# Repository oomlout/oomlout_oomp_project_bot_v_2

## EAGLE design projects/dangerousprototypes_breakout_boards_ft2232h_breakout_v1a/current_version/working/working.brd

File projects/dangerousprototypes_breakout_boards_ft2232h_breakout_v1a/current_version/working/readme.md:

# breakout_boards
 
## summary 
* id: dangerousprototypes_breakout_boards_ft2232h_breakout_v1a
* user: dangerousprototypes
* name: breakout_boards
* board: ft2232h_breakout_v1a
* repo: https://github.com/DangerousPrototypes/Breakout_Boards

* src_file_repo_sch: 
* src_file_repo_sch_link: https://github.com/DangerousPrototypes/Breakout_Boards/tree/master/
* full details link: https://github.com/oomlout/oomlout_oomp_project_bot_v_2/tree/main/projects/dangerousprototypes_breakout_boards_ft2232h_breakout_v1a/current_version/working

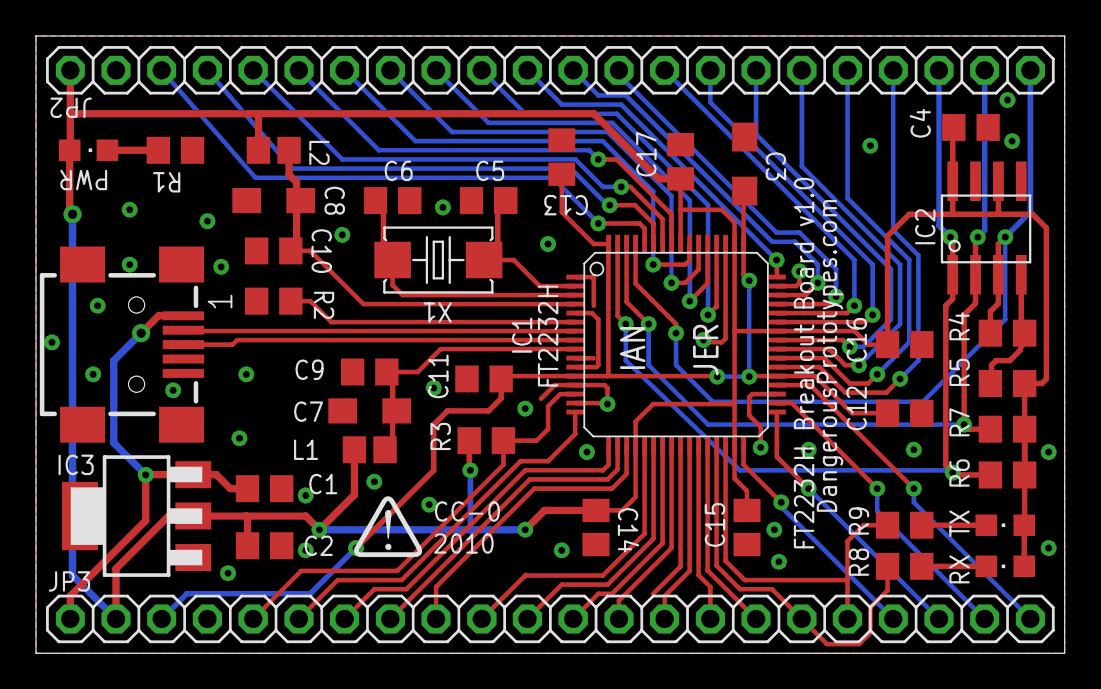
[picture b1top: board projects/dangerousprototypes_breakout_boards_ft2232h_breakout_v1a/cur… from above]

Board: 2 copper layers, 57.1 x 34.3 mm, 40 parts (1 on the bottom side), 53 nets.

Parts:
C1, C2, C4, C9, C10, C11, C12, C13, C14, C15, C16, C17: 0.1uF; C805
C3: 3.3uF; SMC_A
C5, C6: 27pF; C805
C7, C8: 4.7uF; SMC_A
CONN1: CONN_USB; CONN_USB_MINI-B
IC1: FT2232H; LQFP64
IC2: 93C46; SOIC8
IC3: SOT223
JP2, JP3: 1X22
L1, L2: FB805
PWR: LED-805
R1, R8, R9: 470; R805
R2: 12k 1%; R805
R3, R5, R6, R7: 10k; R805
R4: 2.2k; R805
RX: LED-805
TX: LED-805
U$7, U$8: DP_LOGO
X1: 12MHz; 4X6

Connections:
1.8V: C3.+, C11.1, C12.1, C13.1, IC1.12, IC1.37, IC1.49, IC1.64, JP3.3
3.3V: C2.1, C4.1, C14.1, C15.1, C16.1, C17.1, IC1.20, IC1.31, IC1.42, IC1.50, IC1.56, IC2.6, IC2.8, IC3.2, JP2.1, JP3.2, L1.2, L2.2, PWR.A, R3.1, R5.2, R6.2, R7.2, RX.A, TX.A
5V: C1.1, CONN1.VUSB, IC3.3, JP3.1
!PWEREN: IC1.60, JP2.3
!RESET: IC1.14, JP3.5, R3.2
!SUSPEND: IC1.36, JP3.22
AC0: IC1.26, JP3.14
AC1: IC1.27, JP3.15
AC2: IC1.28, JP3.16
AC3: IC1.29, JP3.17, R8.1
AC4: IC1.30, JP3.18, R9.1
AC5: IC1.32, JP3.19
AC6: IC1.33, JP3.20
AC7: IC1.34, JP3.21
AD0: IC1.16, JP3.6
AD1: IC1.17, JP3.7
AD2: IC1.18, JP3.8
AD3: IC1.19, JP3.9
AD4: IC1.21, JP3.10
AD5: IC1.22, JP3.11
AD6: IC1.23, JP3.12
AD7: IC1.24, JP3.13
BC0: IC1.48, JP2.11
BC1: IC1.52, JP2.10
BC2: IC1.53, JP2.9
BC3: IC1.54, JP2.8
BC4: IC1.55, JP2.7
BC5: IC1.57, JP2.6
BC6: IC1.58, JP2.5
BC7: IC1.59, JP2.4
BD0: IC1.38, JP2.19
BD1: IC1.39, JP2.18
BD2: IC1.40, JP2.17
BD3: IC1.41, JP2.16
BD4: IC1.43, JP2.15
BD5: IC1.44, JP2.14
BD6: IC1.45, JP2.13
BD7: IC1.46, JP2.12
DM: CONN1.D-, IC1.7
DP: CONN1.D+, IC1.8
EECLK: IC1.62, IC2.2, JP2.21, R7.1
EECS: IC1.63, IC2.1, JP2.20, R6.1
EEDATA: IC1.61, IC2.3, JP2.22, R4.2
GND: C1.2, C2.2, C3.-, C4.2, C5.2, C6.2, C7.-, C8.-, C9.2, C10.2, C11.2, C12.2, C13.2, C14.2, C15.2, C16.2, C17.2, CONN1.GND, IC1.1, IC1.5, IC1.10, IC1.11, IC1.13, IC1.15, IC1.25, IC1.35, IC1.47, IC1.51, IC2.5, IC3.1, JP2.2, JP3.4, R1.1, R2.1
unnamed: PWR.C, R1.2
unnamed: R8.2, RX.C
unnamed: R9.2, TX.C
unnamed: IC1.6, R2.2
unnamed: C5.1, IC1.2, X1.1
unnamed: C6.1, IC1.3, X1.2
unnamed: IC2.4, R4.1, R5.1
unnamed: C8.+, C10.1, IC1.4, L2.1
unnamed: C7.+, C9.1, IC1.9, L1.1

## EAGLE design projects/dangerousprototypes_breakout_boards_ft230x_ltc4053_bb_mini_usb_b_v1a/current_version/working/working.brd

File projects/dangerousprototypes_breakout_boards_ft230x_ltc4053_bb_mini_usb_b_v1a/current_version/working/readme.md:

# breakout_boards
 
## summary 
* id: dangerousprototypes_breakout_boards_ft230x_ltc4053_bb_mini_usb_b_v1a
* user: dangerousprototypes
* name: breakout_boards
* board: ft230x_ltc4053_bb_mini_usb_b_v1a
* repo: https://github.com/DangerousPrototypes/Breakout_Boards

* src_file_repo_sch: 
* src_file_repo_sch_link: https://github.com/DangerousPrototypes/Breakout_Boards/tree/master/
* full details link: https://github.com/oomlout/oomlout_oomp_project_bot_v_2/tree/main/projects/dangerousprototypes_breakout_boards_ft230x_ltc4053_bb_mini_usb_b_v1a/current_version/working

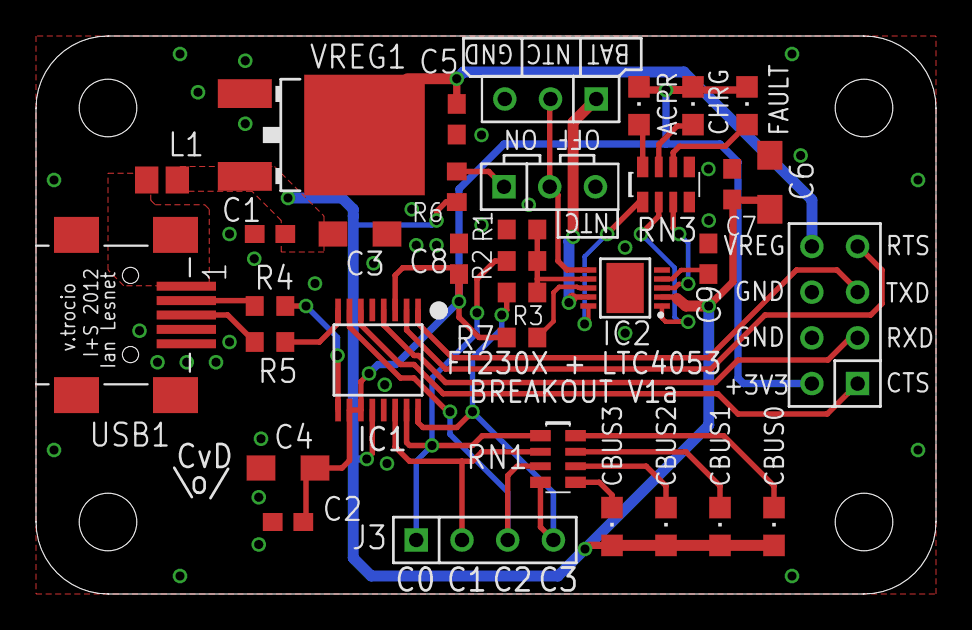
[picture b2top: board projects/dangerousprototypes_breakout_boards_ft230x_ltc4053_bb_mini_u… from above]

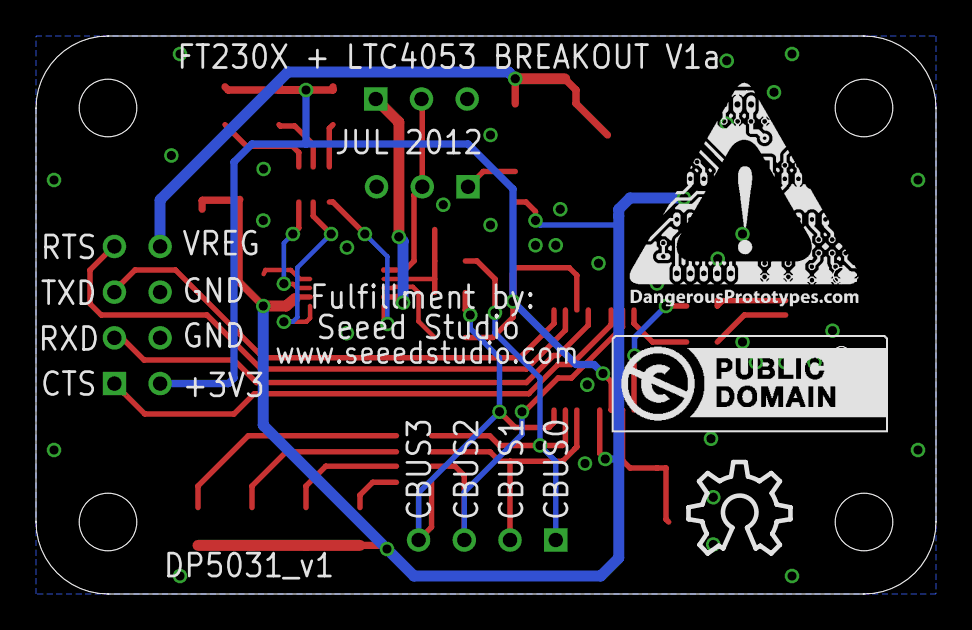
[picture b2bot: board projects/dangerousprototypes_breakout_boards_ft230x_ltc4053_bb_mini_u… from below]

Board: 2 copper layers, 50.0 x 31.0 mm, 39 parts (3 on the bottom side), 33 nets.

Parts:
ACPR: LED-805
C1, C2: C603
C3, C4: SMC_A
C5, C7, C8, C9: 0.1uF; C603
C6: 4.7uF 10V; SMC_A
CHRG: LED-805
D1, D2, D3, D4: LED-805
FAULT: LED-805
IC1: IC_FT230X-SSOP-16; SSOP-16-FTDI
IC2: IC_LTC4053-MSOP-10; MSOP-10
J1, J4: CON_HEADER_1X03-PTH; M1X3
J3: CON_HEADER_1X04; M1X4
J5: CON_HEADER_2X04-PTH; M2X4
L1: 600R 2A; FB603
PCB1: PCB_DP_RECTANGLE-31X50; DP5031_V1
R1: 16.5K 1%; R603
R2: 1.5K 1%; R603
R3, R6: 4.32K 1%; R603
R4, R5: 27R; R603
R7: 10K; R603
RN1: RN8P-4R-CRA06S
RN3: 470R; RN8P-4R-CRA06S
U$1: FRAME_DINA4_L; DP_LOGO
U$3: DP_LOGO_ART_0.5X0.5
U$4: LOGO_CC-0
U$5: OSHW_10X200_NOTEXT
USB1: CON-USB-F-MINI-B; CONN_USB_MINI-B
VREG1: DPAK

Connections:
+3V3: ACPR.C, C2.1, C4.+, C8.1, CHRG.C, FAULT.C, IC1.3, IC1.10, IC1.11, J5.2, R7.2
BAT: IC2.P9, J1.1
CBUS0: IC1.15, J3.1, R2.2, RN1.1
CBUS1: IC1.14, J3.2, RN1.2
CBUS2: IC1.7, J3.3, RN1.3
CBUS3: IC1.16, J3.4, R3.2, RN1.4
CTS: IC1.6, J5.1
GND: C1.2, C2.2, C3.-, C4.-, C5.2, C6.-, C7.2, C8.2, C9.2, IC1.5, IC1.13, IC2.P5, IC2.P11, J1.3, J4.3, J5.4, J5.6, R1.1, USB1.GND, VREG1.1
unnamed: IC2.P10, RN3.1
unnamed: IC2.P7, R1.2, R2.1, R3.1
unnamed: IC2.P1, RN3.2
unnamed: IC2.P3, RN3.3
unnamed: D1.C, RN1.8
unnamed: D2.C, RN1.7
unnamed: D3.C, RN1.6
unnamed: D4.C, RN1.5
unnamed: IC2.P8, R7.1
unnamed: J4.1, R6.1
unnamed: IC1.9, R4.2
unnamed: IC1.8, R5.2
unnamed: C9.1, IC2.P4
unnamed: FAULT.A, RN3.6
unnamed: CHRG.A, RN3.7
unnamed: ACPR.A, RN3.8
NTC: IC2.P6, J1.2, J4.2
RTS: IC1.2, J5.7
RXD: IC1.4, J5.3
TXD: IC1.1, J5.5
USBD+: R5.1, USB1.D+
USBD-: R4.1, USB1.D-
V+: C1.1, C3.+, C6.+, C7.1, D1.A, D2.A, D3.A, D4.A, IC1.12, IC2.P2, L1.1, R6.2, VREG1.3
VREG: C5.1, J5.8, VREG1.2
VUSBE: L1.2, USB1.VUSB

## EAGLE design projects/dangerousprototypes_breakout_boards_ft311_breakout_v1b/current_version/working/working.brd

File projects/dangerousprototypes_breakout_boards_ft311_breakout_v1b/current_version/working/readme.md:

# breakout_boards
 
## summary 
* id: dangerousprototypes_breakout_boards_ft311_breakout_v1b
* user: dangerousprototypes
* name: breakout_boards
* board: ft311_breakout_v1b
* repo: https://github.com/DangerousPrototypes/Breakout_Boards

* src_file_repo_sch: 
* src_file_repo_sch_link: https://github.com/DangerousPrototypes/Breakout_Boards/tree/master/
* full details link: https://github.com/oomlout/oomlout_oomp_project_bot_v_2/tree/main/projects/dangerousprototypes_breakout_boards_ft311_breakout_v1b/current_version/working

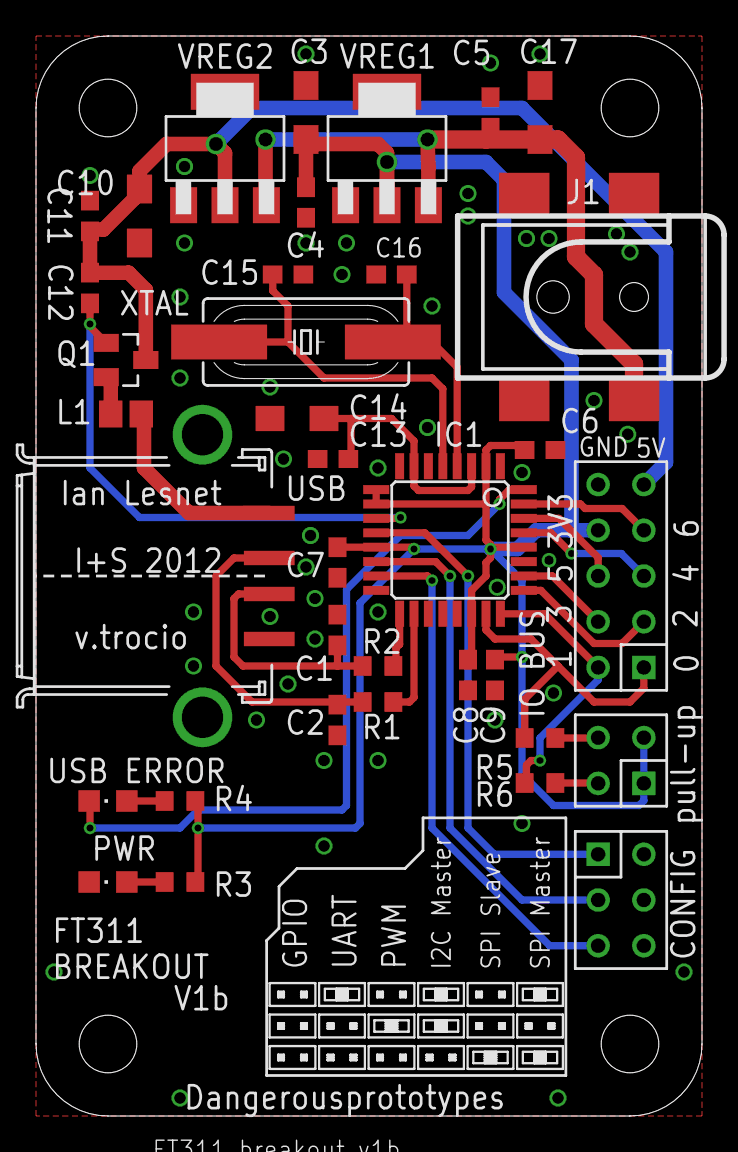
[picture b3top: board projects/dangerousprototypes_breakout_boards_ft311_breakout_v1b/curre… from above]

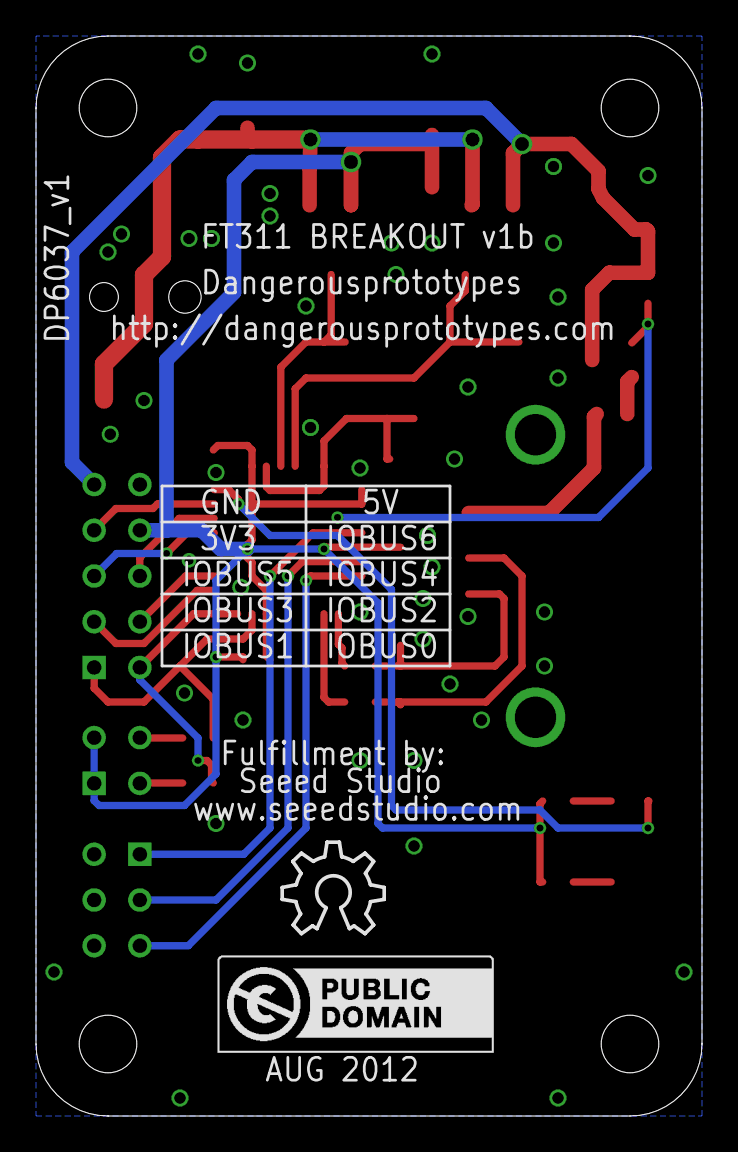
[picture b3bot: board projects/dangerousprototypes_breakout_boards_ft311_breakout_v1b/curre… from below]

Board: 2 copper layers, 37.0 x 60.0 mm, 62 parts (2 on the bottom side), 29 nets.

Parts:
C1, C2: 47pF; C603
C3, C10, C14, C17: 10uF; SMC_A
C4, C5, C6, C7, C8, C9, C11, C12, C13: 0.1uF; C603
C15, C16: 18pF; C603
IC1: IC_FT311D-LQFP-32; LQFP-32
J1: DC_BARREL_JACK_SMD_2MM
J2: CON_HEADER_2X03-PTH; M2X3
J3: CON_HEADER_2X02-PTH; M2X2
J4: CON_HEADER_2X05-PTH; M2X5
L1: 1.7A; FB603
LED1: YELLOW; LED-805
LED2: RED; LED-805
PCB1: PCB_DP_RECTANGLE-37X60; DP6037_V1
Q1: SOT-23
R1, R2: 27R; R603
R3: 3.3K; R603
R4: 1.2K; R603
R5, R6: 10K; R603
U$1: FRAME_DINA4_L; DP_LOGO
U$2, U$4, U$10, U$11, U$12, U$13, U$14, U$15, U$16, U$17, U$19, U$23, U$25: JUMP2_DESC_OFF
U$3, U$5, U$6, U$7, U$8, U$9, U$18, U$22, U$24: JUMP2_DESC_ON
U$20: LOGO_CC-0
U$21: OSHW_8X200_NOTEXT
USB: CON-USB-F-2PB; CONN_USB_A_F
VREG1: LD1117S33; SOT-223
VREG2: LD1117S50; SOT-223
XTAL: 12Mhz; HC-49U

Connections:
!USB_ERR: IC1.32, LED2.C
!VBUSCTRL: C12.2, IC1.11, Q1.1
+1V8: C13.1, C14.+, IC1.3, IC1.7
+3V3: C3.+, C4.1, C6.1, C7.1, C8.1, C9.1, IC1.2, IC1.9, IC1.10, IC1.13, IC1.22, IC1.28, J3.1, J3.3, J4.8, R3.2, R4.2, VREG1.2
+5V: C10.+, C11.1, C12.1, J4.9, Q1.3, VREG2.2
CNFG0: IC1.12, J2.1
CNFG1: IC1.14, J2.3
CNFG2: IC1.15, J2.5
GND: C1.2, C2.2, C3.-, C4.2, C5.2, C6.2, C7.2, C8.2, C9.2, C10.-, C11.2, C13.2, C14.-, C15.2, C16.2, C17.-, IC1.1, IC1.6, IC1.8, IC1.16, IC1.19, IC1.27, J1.P2, J1.P3, J2.2, J2.4, J2.6, J4.10, LED1.C, USB.4, VREG1.1, VREG2.1
IOBUS0: IC1.23, J4.1, R5.1
IOBUS1: IC1.24, J4.2, R6.1
IOBUS2: IC1.25, J4.3
IOBUS3: IC1.26, J4.4
IOBUS4: IC1.29, J4.5
IOBUS5: IC1.30, J4.6
IOBUS6: IC1.31, J4.7
unnamed: IC1.18, R1.1
unnamed: IC1.17, R2.1
unnamed: C1.1, R2.2, USB.3
unnamed: C2.1, R1.2, USB.2
unnamed: L1.2, USB.1
unnamed: L1.1, Q1.2
unnamed: C16.1, IC1.4, XTAL.2
unnamed: C5.1, C17.+, J1.P1@2, VREG1.3, VREG2.3
unnamed: C15.1, IC1.5, XTAL.1
unnamed: LED1.A, R3.1
unnamed: LED2.A, R4.1
unnamed: J3.4, R5.2
unnamed: J3.2, R6.2

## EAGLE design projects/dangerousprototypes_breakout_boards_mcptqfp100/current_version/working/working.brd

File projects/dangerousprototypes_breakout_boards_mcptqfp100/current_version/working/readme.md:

# breakout_boards
 
## summary 
* id: dangerousprototypes_breakout_boards_mcptqfp100
* user: dangerousprototypes
* name: breakout_boards
* board: mcptqfp100
* repo: https://github.com/DangerousPrototypes/Breakout_Boards

* src_file_repo_sch: 
* src_file_repo_sch_link: https://github.com/DangerousPrototypes/Breakout_Boards/tree/master/
* full details link: https://github.com/oomlout/oomlout_oomp_project_bot_v_2/tree/main/projects/dangerousprototypes_breakout_boards_mcptqfp100/current_version/working

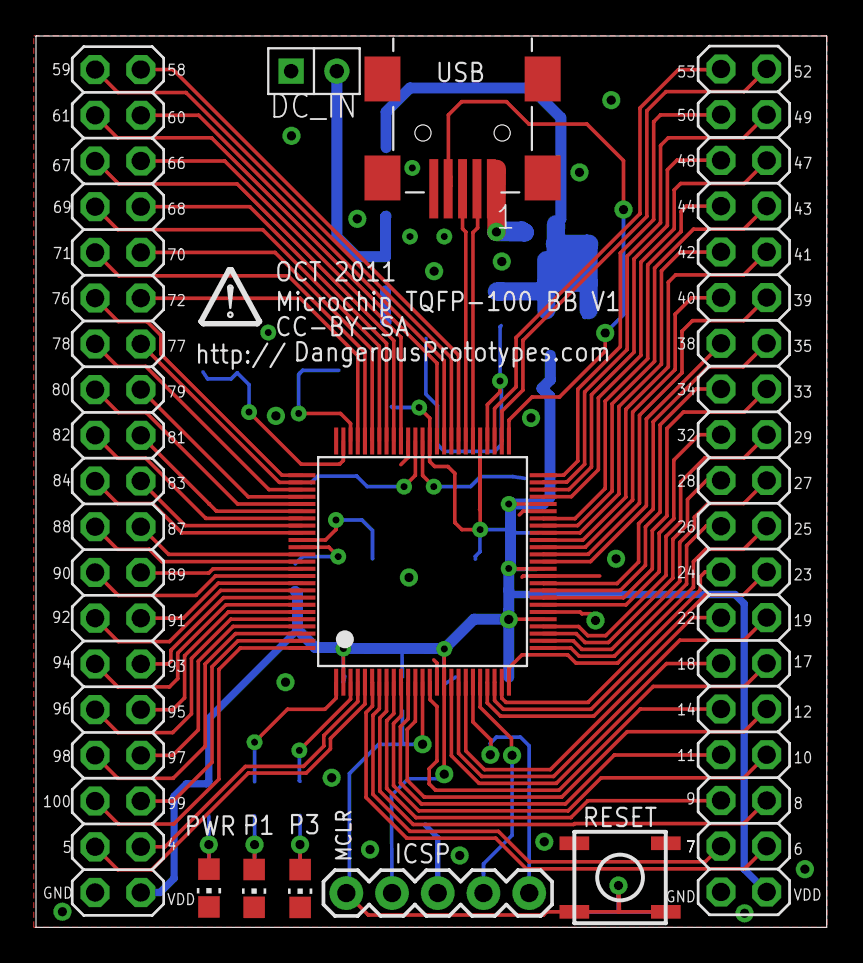
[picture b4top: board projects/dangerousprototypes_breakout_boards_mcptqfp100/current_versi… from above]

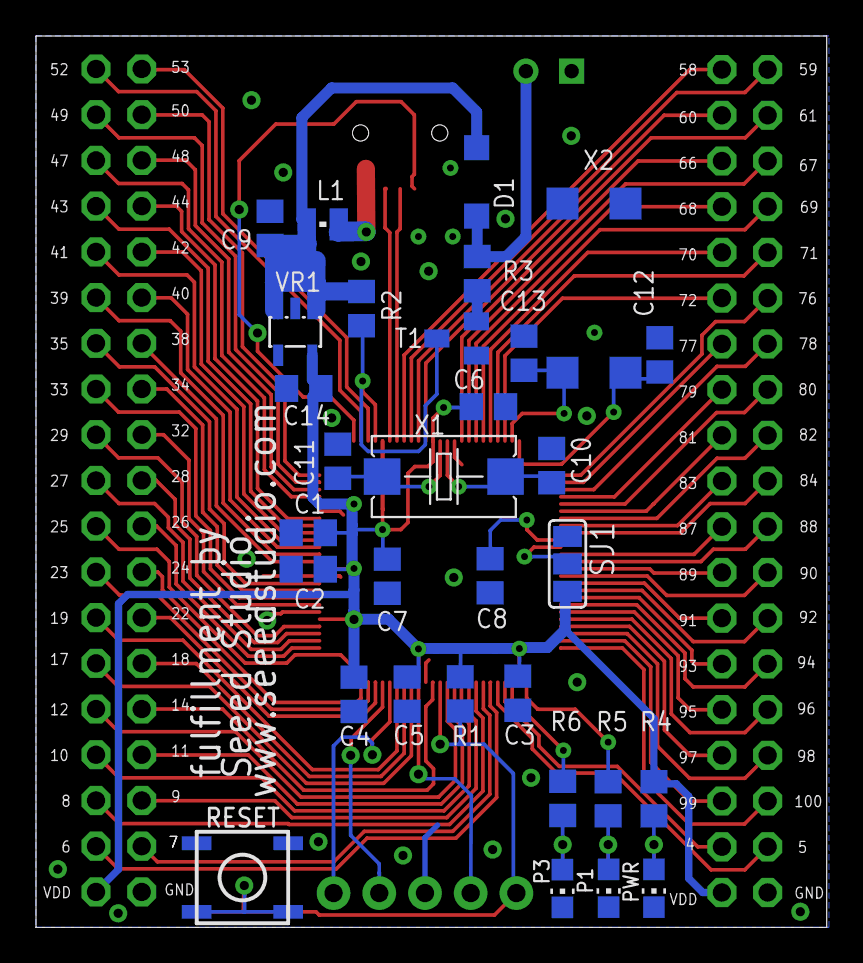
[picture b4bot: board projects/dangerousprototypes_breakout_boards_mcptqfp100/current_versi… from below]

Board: 2 copper layers, 43.9 x 49.5 mm, 42 parts (31 on the bottom side), 96 nets.

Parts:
C1, C2, C3, C4, C5, C6, C7: 0.1uF; C805
C8, C9, C10, C11, C12, C13: 10uF; C805
C14: 1uF; C805
D1: SOD123
DC_IN: HEADER1X2PTH; M1X2
IC1: PIC24FJ256GB210; DP_DEVICES_TQFP100-12MMX12MM
ICSP: 1X05
JP1, JP2: 2X19
L1: WE-KI_0805_B
P1, P2, P3, P4: P4; CHIP-LED0805
PWR, PWR1: P4; CHIP-LED0805
R1: 2K; R805
R2: 100k; R805
R3: 2k; R805
R4, R5, R6: 300; R805
RESET, RESET1: TACT_SWITCH_SMALL
SJ1: SJ_2
T1: SOT23-EBC
U$1: DINA4_L; DP_LOGO
USB: CON-USB-MINI-BUSB1; CONN_USB_MINI-B
VR1: SOT-23-5
X1: OSC-XTAL28M_; 5X8
X2: OSC-32.768; CM309S

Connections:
1: IC1.P1, R5.2
3: IC1.P3, R6.2
4: IC1.P4, JP2.36
5: IC1.P5, JP2.35
6: IC1.P6, JP1.36
7: IC1.P7, JP1.35
8: IC1.P8, JP1.34
9: IC1.P9, JP1.33
10: IC1.P10, JP1.32
11: IC1.P11, JP1.31
12: IC1.P12, JP1.30
14: IC1.P14, JP1.29
17: IC1.P17, JP1.28
18: IC1.P18, JP1.27
19: IC1.P19, JP1.26
22: IC1.P22, JP1.25
23: IC1.P23, JP1.24
24: IC1.P24, JP1.23
25: IC1.P25, JP1.22
26: IC1.P26, JP1.21
27: IC1.P27, JP1.20
28: IC1.P28, JP1.19
29: IC1.P29, JP1.18
32: IC1.P32, JP1.17
33: IC1.P33, JP1.16
34: IC1.P34, JP1.15
35: IC1.P35, JP1.14
38: IC1.P38, JP1.13
39: IC1.P39, JP1.12
40: IC1.P40, JP1.11
41: IC1.P41, JP1.10
42: IC1.P42, JP1.9
43: IC1.P43, JP1.8
44: IC1.P44, JP1.7
47: IC1.P47, JP1.6
48: IC1.P48, JP1.5
49: IC1.P49, JP1.4
50: IC1.P50, JP1.3
52: IC1.P52, JP1.2
53: IC1.P53, JP1.1
58: IC1.P58, JP2.2
59: IC1.P59, JP2.1
60: IC1.P60, JP2.4
61: IC1.P61, JP2.3
66: IC1.P66, JP2.6
67: IC1.P67, JP2.5
68: IC1.P68, JP2.8
69: IC1.P69, JP2.7
70: IC1.P70, JP2.10
71: IC1.P71, JP2.9
72: IC1.P72, JP2.12
76: IC1.P76, JP2.11
77: IC1.P77, JP2.14
78: IC1.P78, JP2.13
79: IC1.P79, JP2.16
80: IC1.P80, JP2.15
81: IC1.P81, JP2.18
82: IC1.P82, JP2.17
83: IC1.P83, JP2.20
84: IC1.P84, JP2.19
87: IC1.P87, JP2.22
88: IC1.P88, JP2.21
89: IC1.P89, JP2.24
90: IC1.P90, JP2.23
91: IC1.P91, JP2.26
92: IC1.P92, JP2.25
93: IC1.P93, JP2.28
94: IC1.P94, JP2.27
95: IC1.P95, JP2.30
96: IC1.P96, JP2.29
97: IC1.P97, JP2.32
98: IC1.P98, JP2.31
99: IC1.P99, JP2.34
100: IC1.P100, JP2.33
D+: IC1.P57, USB.D+
D-: IC1.P56, USB.D-
DCIN: D1.A, DC_IN.2, R3.1
GND: C1.1, C2.1, C3.1, C4.1, C5.1, C6.1, C7.1, C8.2, C9.2, C10.2, C11.2, C12.2, C13.2, C14.2, DC_IN.1, IC1.P15, IC1.P31, IC1.P36, IC1.P45, IC1.P65, IC1.P75, ICSP.3, JP1.37, JP2.37, P1.C, P2.C, P3.C, P4.C, PWR.C, PWR1.C, RESET.1, RESET.2, RESET1.1, RESET1.2, SJ1.1, T1.E, USB.GND, VR1.2
unnamed: C8.1, IC1.P85
unnamed: R3.2, T1.B
unnamed: IC1.P86, SJ1.2
unnamed: PWR.A, PWR1.A, R4.1
unnamed: P1.A, P4.A, R5.1
unnamed: P2.A, P3.A, R6.1
OSCI: C11.1, IC1.P63, X1.2
OSCO: C10.1, IC1.P64, X1.1
PGC: IC1.P20, ICSP.5
PGD: IC1.P21, ICSP.4
SOSCI: C13.1, IC1.P73, X2.4
SOSCO: C12.1, IC1.P74, X2.1
USBID: IC1.P51, USB.ID
VBUS: IC1.P54, R2.2, T1.C
VDD: C1.2, C2.2, C3.2, C4.2, C5.2, C6.2, C7.2, C14.1, IC1.P2, IC1.P16, IC1.P30, IC1.P37, IC1.P46, IC1.P55, IC1.P62, ICSP.2, JP1.38, JP2.38, R1.2, R4.2, SJ1.3, VR1.5
VUSB: C9.1, D1.C, L1.1, R2.1, VR1.1, VR1.3
VUSBO: L1.2, USB.VUSB
~MCLR: IC1.P13, ICSP.1, R1.1, RESET.3, RESET.4, RESET1.3, RESET1.4

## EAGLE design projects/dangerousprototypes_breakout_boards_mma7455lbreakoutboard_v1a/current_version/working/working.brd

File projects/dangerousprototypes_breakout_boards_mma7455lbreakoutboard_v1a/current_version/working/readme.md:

# breakout_boards
 
## summary 
* id: dangerousprototypes_breakout_boards_mma7455lbreakoutboard_v1a
* user: dangerousprototypes
* name: breakout_boards
* board: mma7455lbreakoutboard_v1a
* repo: https://github.com/DangerousPrototypes/Breakout_Boards

* src_file_repo_sch: 
* src_file_repo_sch_link: https://github.com/DangerousPrototypes/Breakout_Boards/tree/master/
* full details link: https://github.com/oomlout/oomlout_oomp_project_bot_v_2/tree/main/projects/dangerousprototypes_breakout_boards_mma7455lbreakoutboard_v1a/current_version/working

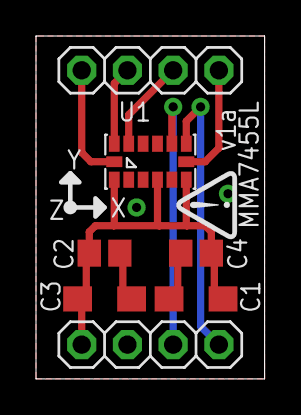
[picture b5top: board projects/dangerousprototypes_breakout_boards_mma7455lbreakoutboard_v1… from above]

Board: 2 copper layers, 12.7 x 19.0 mm, 8 parts (0 on the bottom side), 8 nets.

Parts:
C1, C3: 10uF; SMC_A
C2, C4: 0.1uF; C805
JP1, JP2: 1X04
U1: MMA7455L; LGA-14
U$1: DP_LOGO

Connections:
!CS: JP2.4, U1.7
+3V3: C1.+, C2.1, C3.+, C4.1, JP1.1, U1.1, U1.4, U1.6
GND: C1.-, C2.2, C3.-, C4.2, JP1.2, U1.2, U1.5
INT1/DRDY: JP1.4, U1.8
INT2: JP1.3, U1.9
SCL/SPC: JP2.1, U1.14
SDA/SDI/SDO: JP2.2, U1.13
SDO: JP2.3, U1.12

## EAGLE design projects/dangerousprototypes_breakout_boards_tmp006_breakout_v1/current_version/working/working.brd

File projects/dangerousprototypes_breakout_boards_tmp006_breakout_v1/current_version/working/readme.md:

# breakout_boards
 
## summary 
* id: dangerousprototypes_breakout_boards_tmp006_breakout_v1
* user: dangerousprototypes
* name: breakout_boards
* board: tmp006_breakout_v1
* repo: https://github.com/DangerousPrototypes/Breakout_Boards

* src_file_repo_sch: 
* src_file_repo_sch_link: https://github.com/DangerousPrototypes/Breakout_Boards/tree/master/
* full details link: https://github.com/oomlout/oomlout_oomp_project_bot_v_2/tree/main/projects/dangerousprototypes_breakout_boards_tmp006_breakout_v1/current_version/working

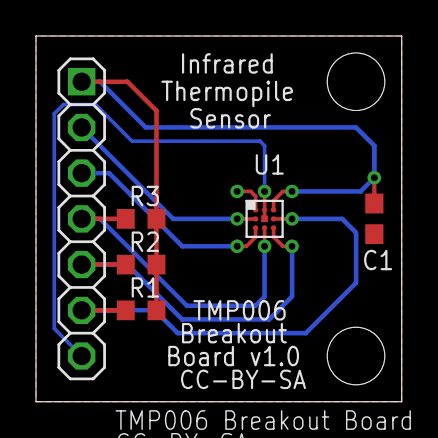
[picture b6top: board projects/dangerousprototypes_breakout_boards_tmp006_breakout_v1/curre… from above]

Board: 2 copper layers, 20.3 x 20.3 mm, 7 parts (0 on the bottom side), 7 nets.

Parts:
C1: 0.1uF; C603
JP1: 1X07
R1, R2, R3: 10k; R603
U1: TMP006; DSBGA-8
U$1: DP_LOGO

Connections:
!DRDY: JP1.4, R3.1, U1.C2
ADR0: JP1.3, U1.C1
ADR1: JP1.2, U1.B1
GND: C1.2, JP1.7, U1.A1, U1.A2
SCL: JP1.6, R1.1, U1.B3
SDA: JP1.5, R2.1, U1.C3
V+: C1.1, JP1.1, R1.2, R2.2, R3.2, U1.A3

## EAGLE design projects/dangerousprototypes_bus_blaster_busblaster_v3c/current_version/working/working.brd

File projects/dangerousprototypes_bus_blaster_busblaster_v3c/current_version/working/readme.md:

# bus_blaster
 
## summary 
* id: dangerousprototypes_bus_blaster_busblaster_v3c
* user: dangerousprototypes
* name: bus_blaster
* board: busblaster_v3c
* repo: https://github.com/DangerousPrototypes/Bus_Blaster

* src_file_repo_sch: 
* src_file_repo_sch_link: https://github.com/DangerousPrototypes/Bus_Blaster/tree/master/
* full details link: https://github.com/oomlout/oomlout_oomp_project_bot_v_2/tree/main/projects/dangerousprototypes_bus_blaster_busblaster_v3c/current_version/working

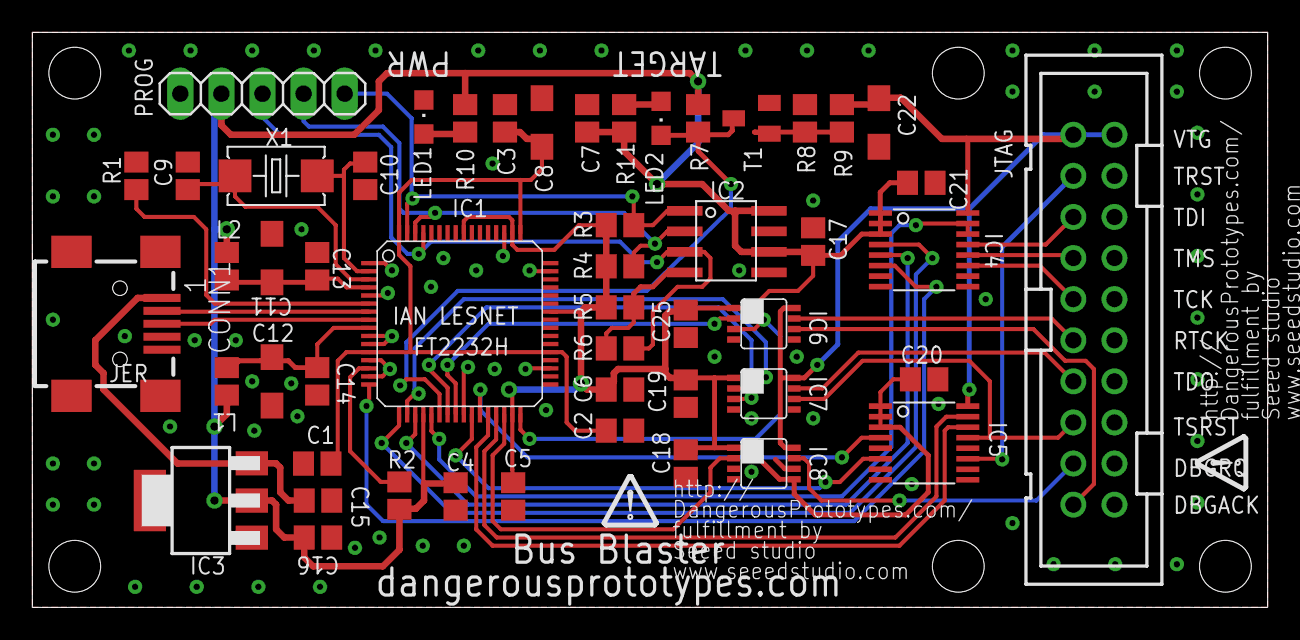
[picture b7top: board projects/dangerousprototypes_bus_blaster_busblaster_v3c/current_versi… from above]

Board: 2 copper layers, 76.3 x 35.5 mm, 54 parts (1 on the bottom side), 43 nets.

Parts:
C1, C2, C3, C4, C5, C6, C7, C13, C14, C15, C16, C17, C18, C19, C20, C21, C25: 100nF; C805
C8: 3.3uF; SMC_A
C9, C10: 27pF; C805
C11, C12, C22: 4.7uF; SMC_A
CONN1: CONN_USB; CONN_USB_MINI-B
IC1: FT2232H; LQFP64
IC2: 93C46; SOIC8
IC3: LD1117-3.3; SOT223
IC4, IC5: TSSOP16
IC6, IC7, IC8: SN74LVC2T45DCTR; DCT_R_PDSO_G8
JTAG: 2520-; PAK100/2500-20
L1, L2: FB805
LED1, LED2: CHIPLED_0805
PROG: 1X05
R1: 12K; R805
R2: 1K; R805
R3, R4, R5, R7: 10K; R805
R6: 2.2K; R805
R8: 100k; R805
R9: 1k; R805
R10, R11: 470; R805
T1: SOT23-BEC
U$1, U$2, U$3: DP_LOGO
X1: CRYSTAL_212M_; 4X6

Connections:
1.8V: C1.2, C2.2, C3.2, C8.+, IC1.12, IC1.37, IC1.49, IC1.64
+3V3: C4.2, C5.2, C6.2, C7.2, C16.2, C17.2, C18.2, C19.2, C20.2, C21.2, C25.2, IC1.20, IC1.31, IC1.42, IC1.50, IC1.56, IC2.6, IC2.8, IC3.2, IC4.1, IC4.2, IC4.3, IC5.1, IC5.2, IC5.3, IC6.1, IC7.1, IC8.1, IC8.5, L1.2, L2.2, PROG.2, R2.1, R3.2, R4.2, R5.2, R7.2, R10.2, R11.2
CS: IC1.63, IC2.1, PROG.5, R3.1
DATA: IC1.61, IC2.3, PROG.3, R6.1
DBGACK: IC1.32, IC6.3
DBGACK-1: IC6.6, JTAG.19
DBGRQ: IC1.30, IC8.2
DBGRQ-1: IC8.7, JTAG.17
DM: CONN1.D-, IC1.7
DO: IC2.4, R5.1, R6.2
DP: CONN1.D+, IC1.8
GND: C1.1, C2.1, C3.1, C4.1, C5.1, C6.1, C7.1, C8.-, C9.2, C10.2, C11.-, C12.-, C13.1, C14.1, C15.1, C16.1, C17.1, C18.1, C19.1, C20.1, C21.1, C22.-, C25.1, CONN1.GND, IC1.1, IC1.5, IC1.10, IC1.11, IC1.13, IC1.15, IC1.25, IC1.35, IC1.47, IC1.51, IC2.5, IC2.7, IC3.1, IC4.7, IC4.8, IC4.9, IC5.5, IC5.7, IC5.8, IC5.9, IC6.4, IC6.5, IC7.4, IC7.5, IC8.4, IC8.6, JTAG.4, JTAG.6, JTAG.8, JTAG.10, JTAG.12, JTAG.14, JTAG.16, JTAG.18, JTAG.20, LED1.C, PROG.1, R1.1, R8.1, T1.E
JTAG_BUFFER_EN: IC1.21, IC4.14, IC4.15
unnamed: C9.1, IC1.3, X1.2
unnamed: C10.1, IC1.2, X1.1
unnamed: IC1.14, R2.2
unnamed: IC1.6, R1.2
unnamed: C15.2, CONN1.VUSB, IC3.3
unnamed: LED1.A, R10.1
unnamed: R8.2, R9.1, T1.B
unnamed: LED2.A, R11.1
RTCK: IC1.24, IC6.2
RTCK-1: IC6.7, JTAG.11
SK: IC1.62, IC2.2, PROG.4, R4.1
TARGET_PRESENT: IC1.22, LED2.C, R7.1, T1.C
TCK1: IC4.11, JTAG.9
TCK/SK/TXD: IC1.16, IC4.6
TDI1: IC4.13, JTAG.5
TDI/DO/RXD: IC1.17, IC4.4
TDO/DI: IC1.18, IC7.2
TDO/DI-1: IC7.7, JTAG.13
TMS1: IC4.12, JTAG.7
TMS/CS: IC1.19, IC4.5
TRST: IC1.26, IC5.6
TRST1: IC5.11, JTAG.3
TRST_BUF_EN: IC1.28, IC5.14
TSRST: IC1.27, IC5.4
TSRST1: IC1.23, IC7.3
TSRST1-1: IC5.13, IC7.6, JTAG.15
TSRST_EN: IC1.29, IC5.15
VPHY: C11.+, C13.2, IC1.4, L2.1
VPLL: C12.+, C14.2, IC1.9, L1.1
V_TARGET: C22.+, IC4.16, IC5.16, IC6.8, IC7.8, IC8.8, JTAG.1, JTAG.2, R9.2
